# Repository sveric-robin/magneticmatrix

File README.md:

# magneticmatrix
A hall-effect / LED matrix that illustrates the nearby magnetic fields, in the hopes of using this as an illustrative tool during EE lectures.

# Notes to self 
linear hall effect sensor (analog out)
TOSHIBA TCS40DLR magnetic sensor --> not sensitive enough (aiming for < mT sensitivities)

analog interfacing circuitry?
MLX sensors have good sensitivity but need a proprietary (expensive) programmer to boost sensitivity
TI DRV5055 (were present in KiCAD) also have analog out and ~20 mT sensitivity--> good fit?

## Remaing questions
- Op amp way seems to have smallest BOM
  - But it does have hard on/off led's
  - opamp package needs to be smaller to decrease pixel spacing
- footprints need to be validated
- stuff needs to be breadboarded, checklist
  - led approach:

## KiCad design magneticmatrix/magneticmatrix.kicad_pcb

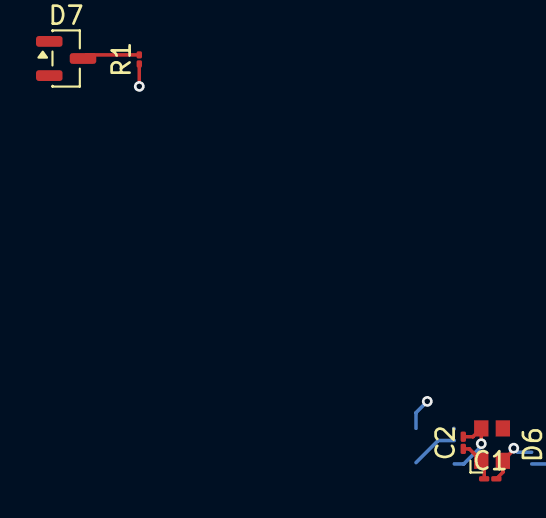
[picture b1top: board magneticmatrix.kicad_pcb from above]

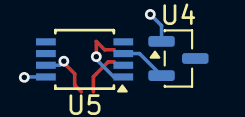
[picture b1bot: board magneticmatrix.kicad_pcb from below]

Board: 4 copper layers, 7 parts (2 on the bottom side), 7 nets.

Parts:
C1, C2: 1u; C_01005_0402Metric_Pad0.57x0.30mm_HandSolder
D6: LED_BGKR; LED_ASMB-KTF0-0A306
D7: BZX84Cxx; SOT-23
R1: 500; R_01005_0402Metric
U4: DRV5055A1xDBZxQ1; SOT-23
U5: TL082; TSSOP-8_3x3mm_P0.65mm

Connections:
/5V: R1.1, U4.1 (VCC), U5.8 (V+)
/Vmid: D7.3 (K), R1.2, U5.2 (-), U5.5 (+)
GND: D6.3 (K), D7.1 (A), U4.3 (GND), U5.4 (V-)
unnamed: C1.1, C2.1, D6.1 (BA)
unnamed: C1.2, D6.2 (GA), U5.7
unnamed: C2.2, D6.4 (RA), U5.1
unnamed: U4.2 (OUT), U5.3 (+), U5.6 (-)

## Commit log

2026-02-20 first unit cells sketch
2026-02-20 RGB instead of bicolor
2026-02-20 Enhance README with detailed project description
    Expanded the project description to include educational use.
2026-02-21 added opamp version
2026-02-21 added some pcb stuff
2026-02-21 Update README with notes and remaining questions
    Added notes and questions regarding components and design considerations for the magnetic matrix project.
